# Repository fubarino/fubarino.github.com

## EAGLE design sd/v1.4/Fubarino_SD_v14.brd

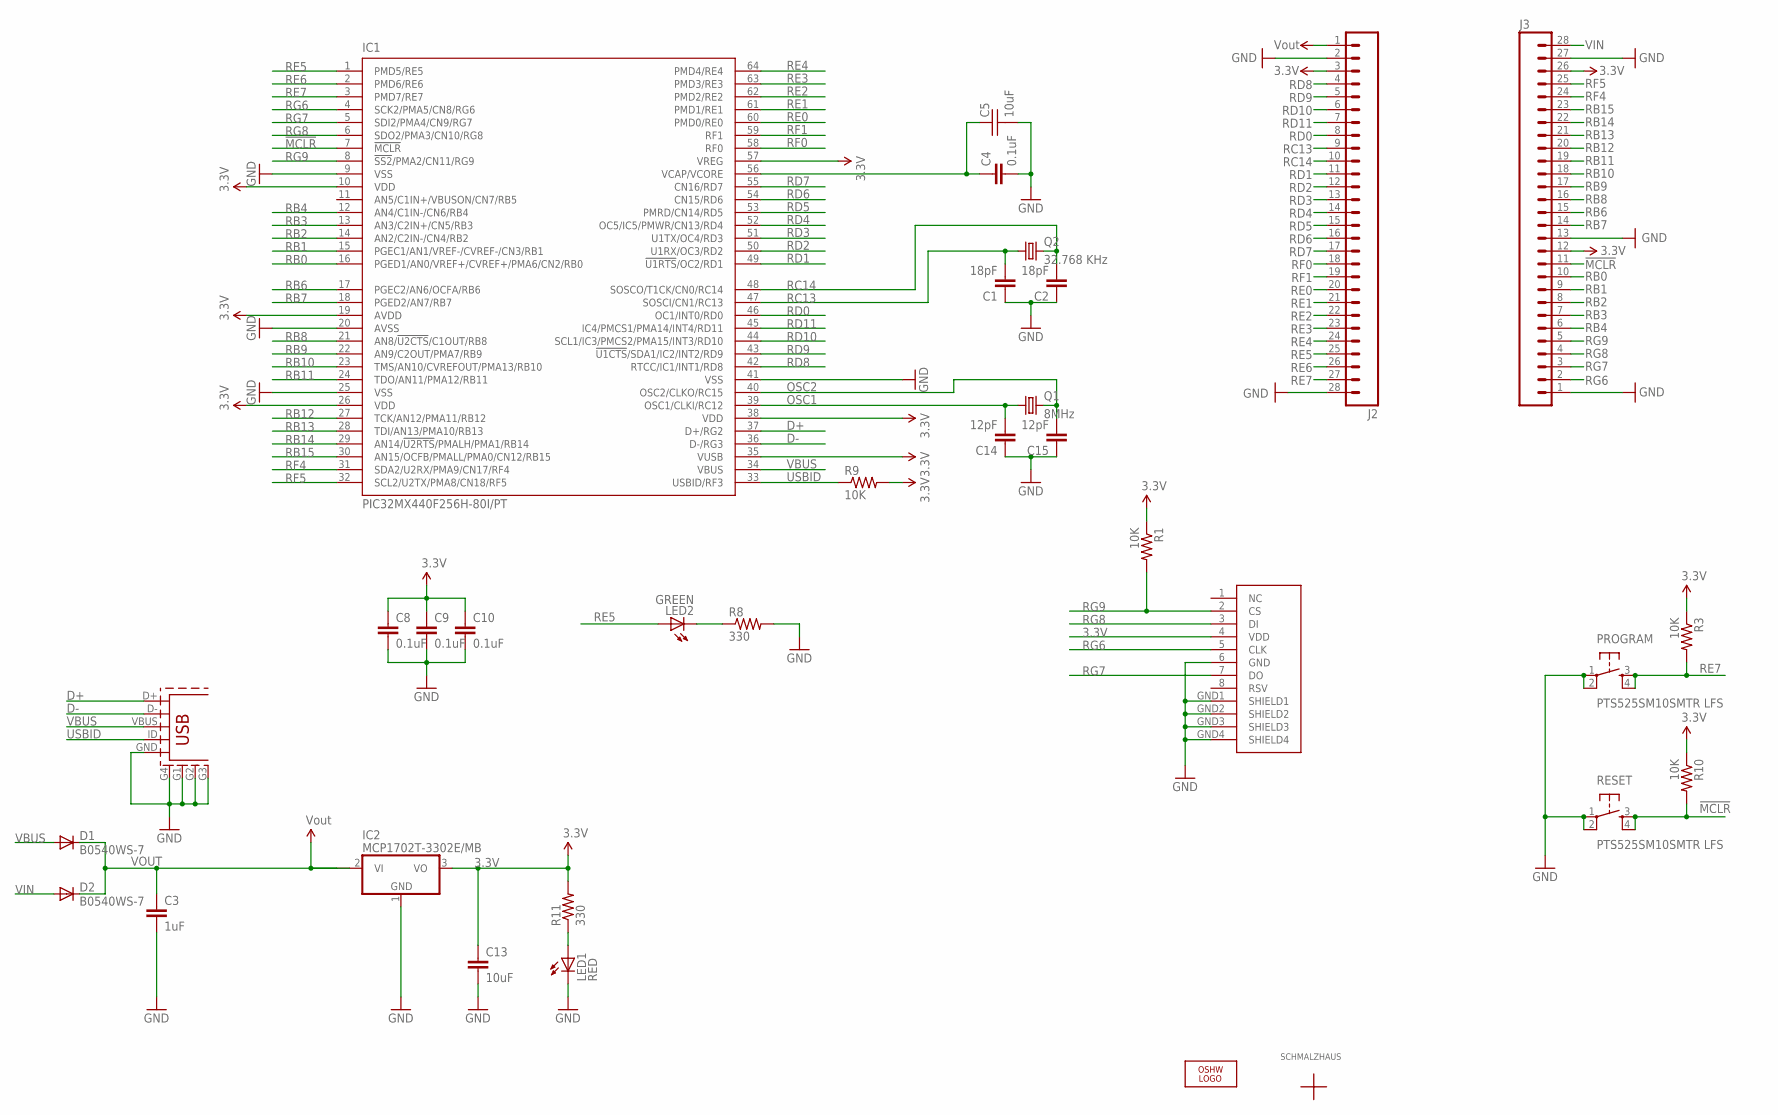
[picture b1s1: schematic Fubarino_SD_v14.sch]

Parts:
C1, C2: 18pF; 0603-CAP
C3: 1uF; 0603-CAP
C4, C8, C9: 0.1uF; 0603-CAP
C5: 10uF; CAP_0805
C10: 0.1uF; 0603
C13: 10uF; 0805
C14, C15: 12pF; 0603-CAP
D1, D2: B0540WS-7; SOD-323
IC1: PIC32MX440F256H-80I/PT; TQFP64-10X10
IC2: MCP1702T-3302E/MB; SOT89
J1: MICRO_SD_CARD_SOCKET; SD-MMC_SOCKET-PP
J2: M28USEPIN1; 1X28
J3: M28NOPIN1; 1X28_NO_PIN_1
J8: UX60A-MB-5ST; USB-MINIB
LED1: RED; LED-0603
LED2: GREEN; LED-0603
LOGO1: OSHW_LOGO_8MILX0070-NT; OSHW_8X70_NOTEXT
PROGRAM: PTS525SM10SMTR LFS; TACTILE_SWITCH_SMD
Q1: 8MHz; NX5032_5MM_3.2MM_CRYSTAL
Q2: 32.768 KHz; TC26H
R1, R3, R9, R10: 10K; 0603-RES
R8, R11: 330; 0603-RES
RESET: PTS525SM10SMTR LFS; TACTILE_SWITCH_SMD
U$1: SCHMALZHAUSSCHMALZHAUS_SMALL; SCHMALZHAUS_SMALL

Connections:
3.3V: C8.1, C9.1, C10.1, C13.1, IC1.10 (VDD), IC1.19 (AVDD), IC1.26 (VDD), IC1.35 (VUSB), IC1.38 (VDD), IC1.57 (VREG), IC2.3 (VO), J1.4 (VDD), J2.3, J3.12, J3.26, R1.1, R3.1, R9.2, R10.1, R11.2
!MCLR!: IC1.7 (!MCLR), J3.11, R10.2, RESET.3, RESET.4
D+: IC1.37 (D+/RG2), J8.D+
D-: IC1.36 (D-/RG3), J8.D-
GND: C1.1, C2.1, C3.2, C4.2, C5.2, C8.2, C9.2, C10.2, C13.2, C14.1, C15.1, IC1.9 (VSS), IC1.20 (AVSS), IC1.25 (VSS), IC1.41 (VSS), IC2.1 (GND), J1.6 (GND), J1.GND1 (SHIELD1), J1.GND2 (SHIELD2), J1.GND3 (SHIELD3), J1.GND4 (SHIELD4), J2.2, J2.28, J3.1, J3.13, J3.27, J8.G1, J8.G2, J8.G3, J8.G4 (SHIELD), J8.GND, LED1.C, PROGRAM.1, PROGRAM.2, R8.2, RESET.1, RESET.2
unnamed: LED1.A, R11.1
unnamed: LED2.C, R8.1
unnamed: C4.1, C5.1, IC1.56 (VCAP/VCORE)
OSC1: C14.2, IC1.39 (OSC1/CLKI/RC12), Q1.1
OSC2: C15.2, IC1.40 (OSC2/CLKO/RC15), Q1.2
RB0: IC1.16 (PGED1/AN0/VREF+/CVREF+/PMA6/CN2/RB0), J3.10
RB1: IC1.15 (PGEC1/AN1/VREF-/CVREF-/CN3/RB1), J3.9
RB2: IC1.14 (AN2/C2IN-/CN4/RB2), J3.8
RB3: IC1.13 (AN3/C2IN+/CN5/RB3), J3.7
RB4: IC1.12 (AN4/C1IN-/CN6/RB4), J3.6
RB6: IC1.17 (PGEC2/AN6/OCFA/RB6), J3.15
RB7: IC1.18 (PGED2/AN7/RB7), J3.14
RB8: IC1.21 (AN8/!U2CTS!/C1OUT/RB8), J3.16
RB9: IC1.22 (AN9/C2OUT/PMA7/RB9), J3.17
RB10: IC1.23 (TMS/AN10/CVREFOUT/PMA13/RB10), J3.18
RB11: IC1.24 (TDO/AN11/PMA12/RB11), J3.19
RB12: IC1.27 (TCK/AN12/PMA11/RB12), J3.20
RB13: IC1.28 (TDI/AN13/PMA10/RB13), J3.21
RB14: IC1.29 (AN14/!U2RTS!/PMALH/PMA1/RB14), J3.22
RB15: IC1.30 (AN15/OCFB/PMALL/PMA0/CN12/RB15), J3.23
RC13: C1.2, IC1.47 (SOSCI/CN1/RC13), J2.9, Q2.1
RC14: C2.2, IC1.48 (SOSCO/T1CK/CN0/RC14), J2.10, Q2.2
RD0: IC1.46 (OC1/INT0/RD0), J2.8
RD1: IC1.49 (!U1RTS!/OC2/RD1), J2.11
RD2: IC1.50 (U1RX/OC3/RD2), J2.12
RD3: IC1.51 (U1TX/OC4/RD3), J2.13
RD4: IC1.52 (OC5/IC5/PMWR/CN13/RD4), J2.14
RD5: IC1.53 (PMRD/CN14/RD5), J2.15
RD6: IC1.54 (CN15/RD6), J2.16
RD7: IC1.55 (CN16/RD7), J2.17
RD8: IC1.42 (RTCC/IC1/INT1/RD8), J2.4
RD9: IC1.43 (!U1CTS!/SDA1/IC2/INT2/RD9), J2.5
RD10: IC1.44 (SCL1/IC3/PMCS2/PMA15/INT3/RD10), J2.6
RD11: IC1.45 (IC4/PMCS1/PMA14/INT4/RD11), J2.7
RE0: IC1.60 (PMD0/RE0), J2.20
RE1: IC1.61 (PMD1/RE1), J2.21
RE2: IC1.62 (PMD2/RE2), J2.22
RE3: IC1.63 (PMD3/RE3), J2.23
RE4: IC1.64 (PMD4/RE4), J2.24
RE5: IC1.1 (PMD5/RE5), J2.25, LED2.A
RE6: IC1.2 (PMD6/RE6), J2.26
RE7: IC1.3 (PMD7/RE7), J2.27, PROGRAM.3, PROGRAM.4, R3.2
RF0: IC1.58 (RF0), J2.18
RF1: IC1.59 (RF1), J2.19
RF4: IC1.31 (SDA2/U2RX/PMA9/CN17/RF4), J3.24
RF5: IC1.32 (SCL2/U2TX/PMA8/CN18/RF5), J3.25
RG6: IC1.4 (SCK2/PMA5/CN8/RG6), J1.5 (CLK), J3.2
RG7: IC1.5 (SDI2/PMA4/CN9/RG7), J1.7 (DO), J3.3
RG8: IC1.6 (SDO2/PMA3/CN10/RG8), J1.3 (DI), J3.4
RG9: IC1.8 (!SS2!/PMA2/CN11/RG9), J1.2 (CS), J3.5, R1.2
USBID: IC1.33 (USBID/RF3), J8.ID (USB_ID), R9.1
VBUS: D1.2 (A), IC1.34 (VBUS), J8.VBUS
VIN: D2.2 (A), J3.28
VOUT: C3.1, D1.1 (C), D2.1 (C), IC2.2 (VI), IC2.2@1 (VI1), J2.1

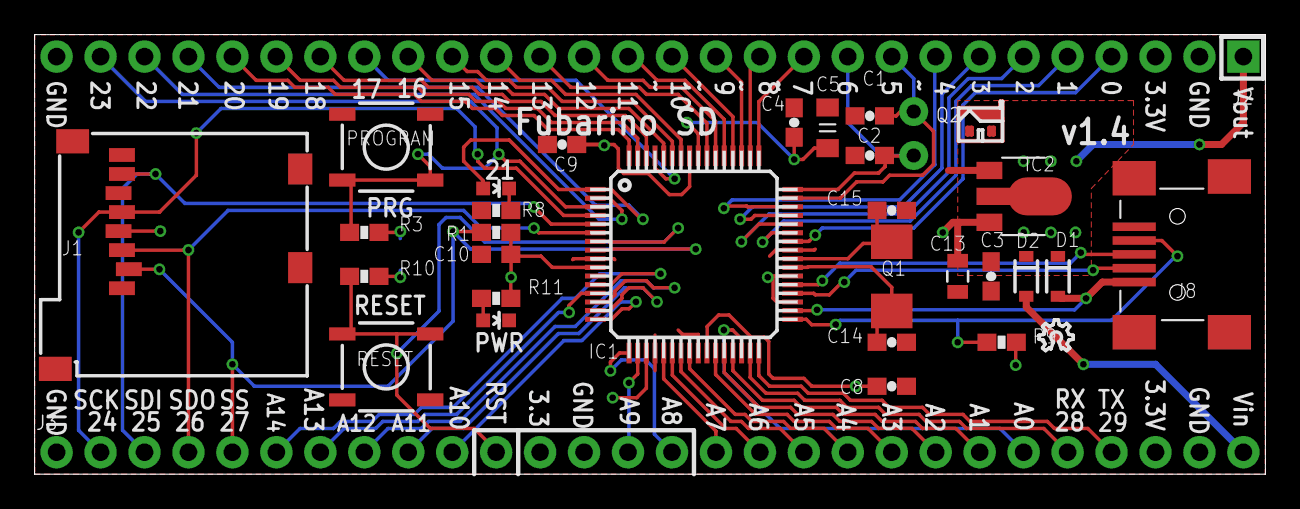
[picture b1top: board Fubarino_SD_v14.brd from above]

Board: 2 copper layers, 71.1 x 25.4 mm, 33 parts (0 on the bottom side), 59 nets.

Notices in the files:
sd/v1.4/Fubarino_SD_v14.brd:
Copyright 2012 Brian Schmalz Copyright and related rights are licensed under the Solderpad Hardware License, Version 0.51 (the “License”);
software, hardware and materials distributed under this License is distributed on an “AS IS” BASIS, WITHOUT WARRANTIES OR CONDITIONS OF ANY KIND, either express or implied.
